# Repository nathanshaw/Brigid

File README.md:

# Brigid
Solenoid Driver

Please note that for each board you much change the ARDUINO_ID to a unique number

If you want to turn off LED feedback change LED_FEEDBACK to 0

If you don't want the startup sequence change BOOT_TEST to 0

If the LED is not yellow during the BOOT_TEST change your led pins until it is.

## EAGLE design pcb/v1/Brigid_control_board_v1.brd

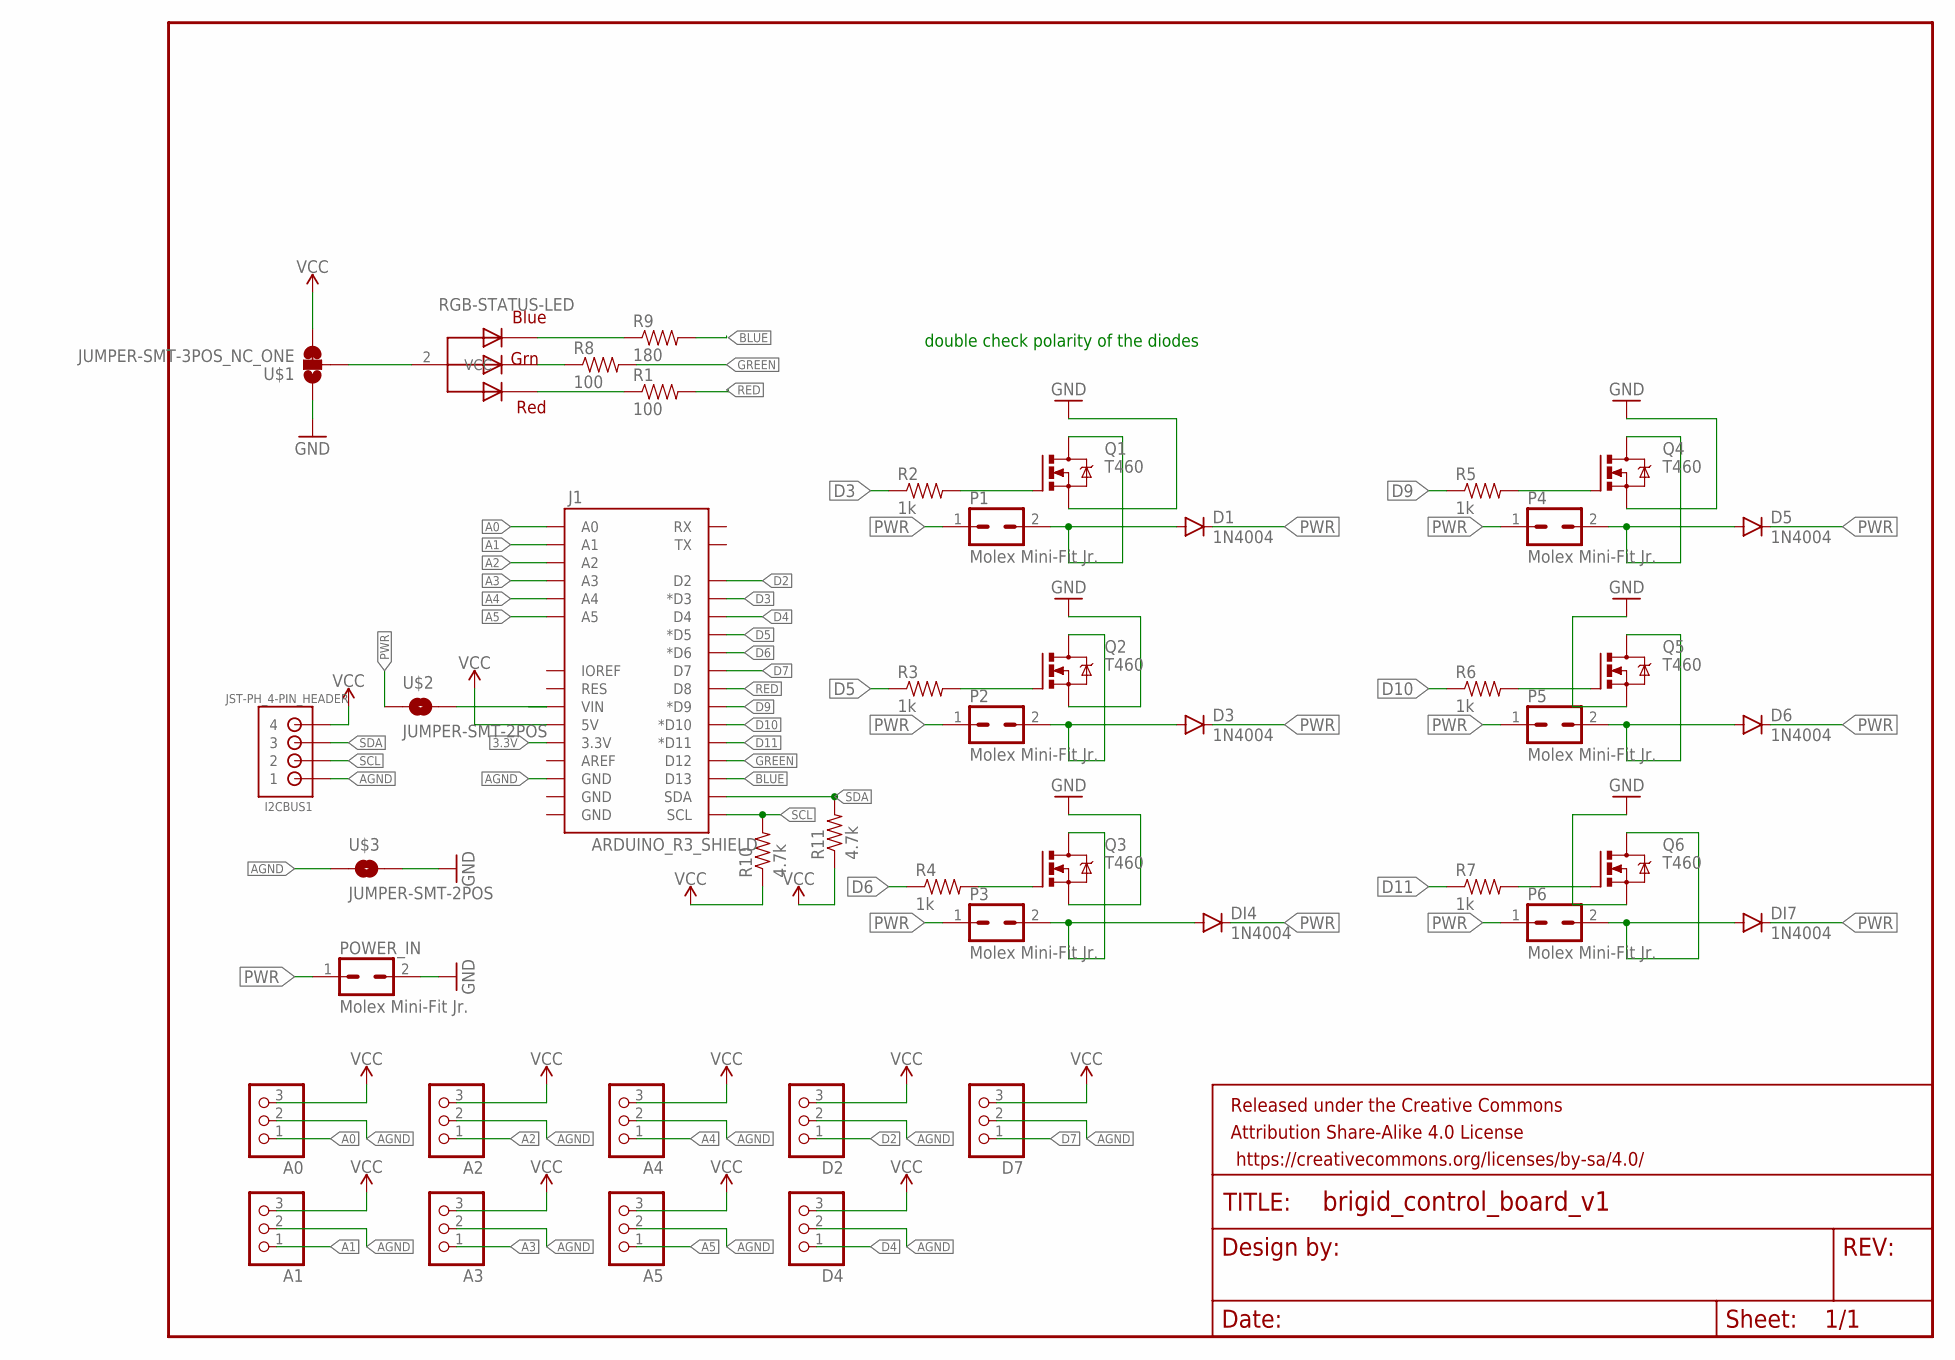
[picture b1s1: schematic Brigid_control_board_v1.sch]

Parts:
A0, A1, A2, A3, A4, A5: PINHD-1X3; 1X03
D1, D3, D5, D6: 1N4004; DIODE-1N4001
D2, D4, D7: PINHD-1X3; 1X03
DI4, DI7: 1N4004; DIODE-1N4001
FRAME1: FRAME-LETTER; CREATIVE_COMMONS
I2CBUS1: JST-PH_4-PIN_HEADER; JST_B4B-PH_HEADER
J1: ARDUINO_R3_SHIELD; UNO_R3_SHIELD
P1, P2, P3, P4, P5, P6: Molex Mini-Fit Jr.; 39-30-?02?
POWER_IN: Molex Mini-Fit Jr.; 39-30-?02?
Q1, Q2, Q3, Q4, Q5, Q6: T460; TO220BV
R1, R8: 100; AXIAL-0.3EZ
R2, R3, R4, R5, R6, R7: 1k; AXIAL-0.3EZ
R9: 180; AXIAL-0.3EZ
R10, R11: 4.7k; AXIAL-0.3EZ
RGB-STATUS-LED: RGB LED; LED5MMRGB
U$1: JUMPER-SMT-3POS_NC_ONE; SMT-JUMPER_3_1-NC_TRACE_NO-SILK
U$2, U$3: JUMPER-SMT-2POS; SMT-JUMPER_2_NO_NO-SILK

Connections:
3.3V: J1.3.3V
A0: A0.1, J1.A0
A1: A1.1, J1.A1
A2: A2.1, J1.A2
A3: A3.1, J1.A3
A4: A4.1, J1.A4
A5: A5.1, J1.A5
AGND: A0.2, A1.2, A2.2, A3.2, A4.2, A5.2, D2.2, D4.2, D7.2, I2CBUS1.P1 (1), J1.GND@2 (GND), U$3.1
BLUE: J1.D13, R9.P$2 (2)
D2: D2.1, J1.D2
D3: J1.D3 (*D3), R2.P$1 (1)
D4: D4.1, J1.D4
D5: J1.D5 (*D5), R3.P$1 (1)
D6: J1.D6 (*D6), R4.P$1 (1)
D7: D7.1, J1.D7
D9: J1.D9 (*D9), R5.P$1 (1)
D10: J1.D10 (*D10), R6.P$1 (1)
D11: J1.D11 (*D11), R7.P$1 (1)
GND: POWER_IN.2, Q1.S, Q2.S, Q3.S, Q4.S, Q5.S, Q6.S, U$1.1, U$3.2
GREEN: J1.D12, R8.P$2 (2)
unnamed: D1.A, P1.2, Q1.D
unnamed: R9.P$1 (1), RGB-STATUS-LED.4 (BLUE)
unnamed: RGB-STATUS-LED.2 (VCC), U$1.2
unnamed: R1.P$1 (1), RGB-STATUS-LED.1 (RED)
unnamed: R8.P$1 (1), RGB-STATUS-LED.3 (GREEN)
unnamed: Q2.G, R3.P$2 (2)
unnamed: D3.A, P2.2, Q2.D
unnamed: Q1.G, R2.P$2 (2)
unnamed: Q3.G, R4.P$2 (2)
unnamed: DI4.A, P3.2, Q3.D
unnamed: Q4.G, R5.P$2 (2)
unnamed: D5.A, P4.2, Q4.D
unnamed: Q5.G, R6.P$2 (2)
unnamed: D6.A, P5.2, Q5.D
unnamed: Q6.G, R7.P$2 (2)
unnamed: DI7.A, P6.2, Q6.D
PWR: D1.C, D3.C, D5.C, D6.C, DI4.C, DI7.C, P1.1, P2.1, P3.1, P4.1, P5.1, P6.1, POWER_IN.1, U$2.1
RED: J1.D8, R1.P$2 (2)
SCL: I2CBUS1.P2 (2), J1.SCL, R10.P$2 (2)
SDA: I2CBUS1.P3 (3), J1.SDA, R11.P$2 (2)
VCC: A0.3, A1.3, A2.3, A3.3, A4.3, A5.3, D2.3, D4.3, D7.3, I2CBUS1.P4 (4), J1.5V, R10.P$1 (1), R11.P$1 (1), U$1.3
VIN: J1.VIN, U$2.2

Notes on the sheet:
double check polarity of the diodes

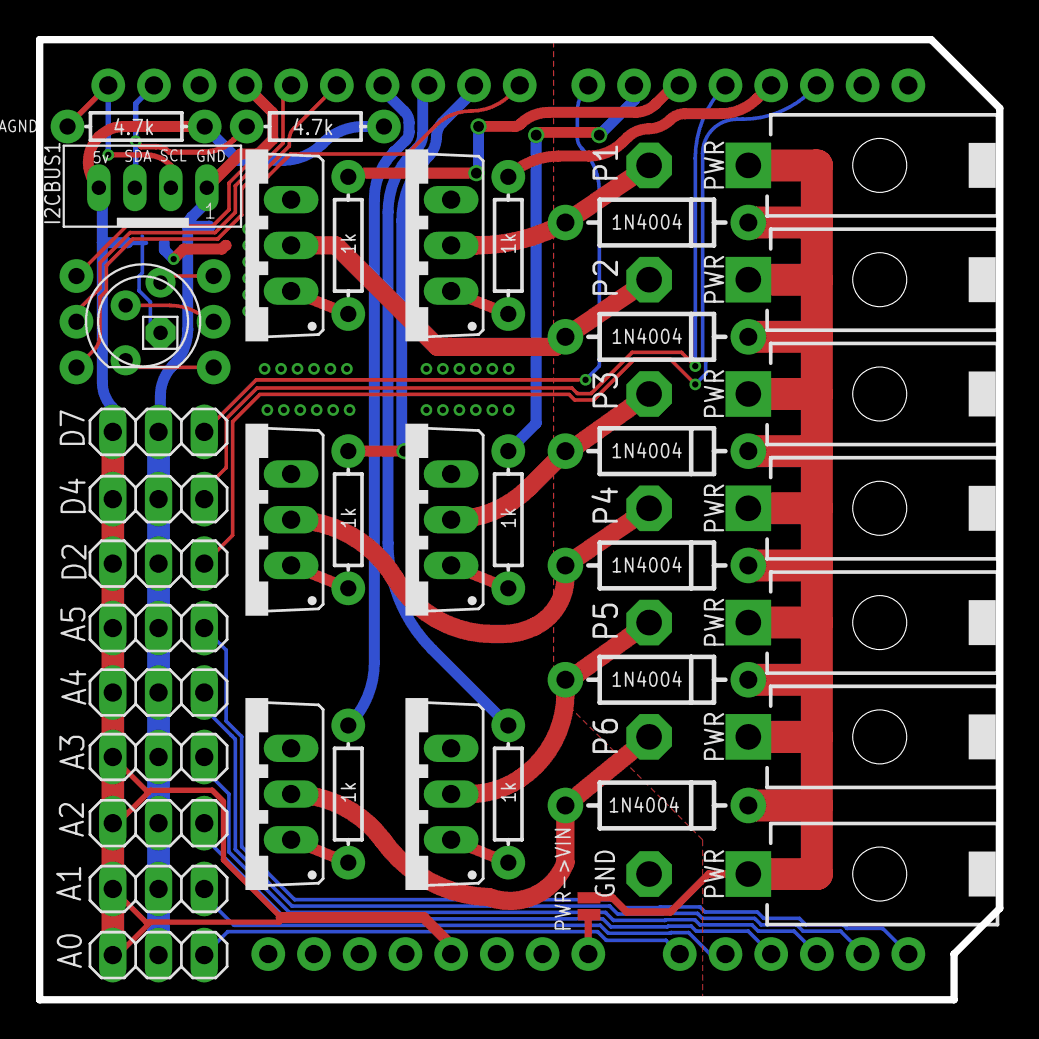
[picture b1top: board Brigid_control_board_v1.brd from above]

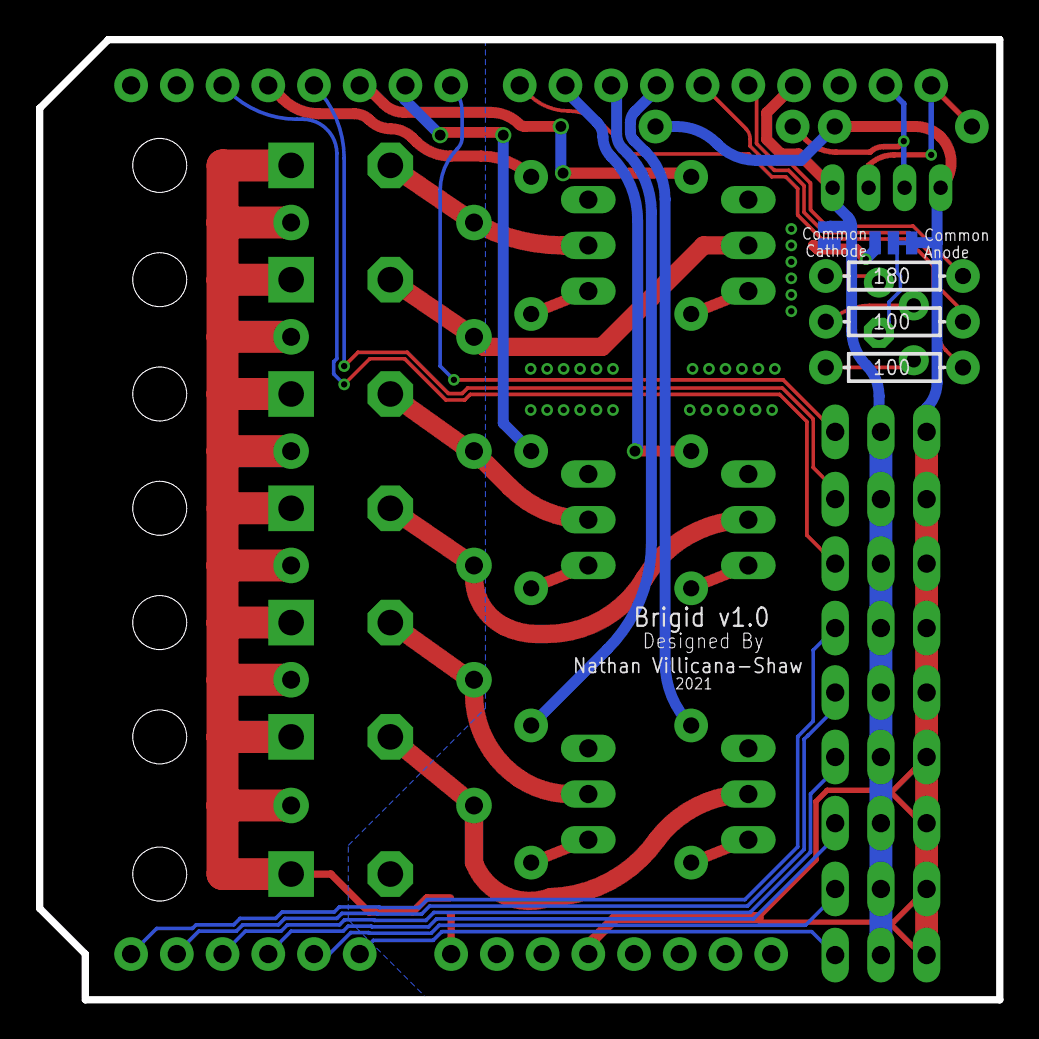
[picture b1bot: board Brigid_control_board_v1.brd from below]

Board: 2 copper layers, 53.3 x 53.3 mm, 46 parts (5 on the bottom side), 41 nets.

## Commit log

2016-11-08 adding brd and sch files to repo
2016-11-14 updated brigid do over
2016-11-19 updated brigid test
2016-12-06 made brigid rev 2, created LED version of code
2016-12-06 updated firmware for brigid
2016-12-13 updated brigid
2017-02-05 moved things around a little
2017-02-05 modified board to be othermill friendly
2017-02-06 got rid of extra firmware
2017-02-15 added firmware for DC_Motors
2017-02-17 updated brigid board, removed switched that were not needed
2017-03-16 got better versions of the firmware
2017-06-07 some house cleaning
2017-06-08 added picture to readme, hopfully
2021-05-23 created the first v1 production version of the board

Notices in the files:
parts and their libraries:
SparkFun-DiscreteSemi: Licensing: Creative Commons ShareAlike 4.0 International - https://creativecommons.org/licenses/by-sa/4.0
con-molex-mini-fit: Copyright (C) 2011, Bob Starr
SparkFun-Aesthetics: Released under the Creative Commons Attribution Share-Alike 4.0 License
